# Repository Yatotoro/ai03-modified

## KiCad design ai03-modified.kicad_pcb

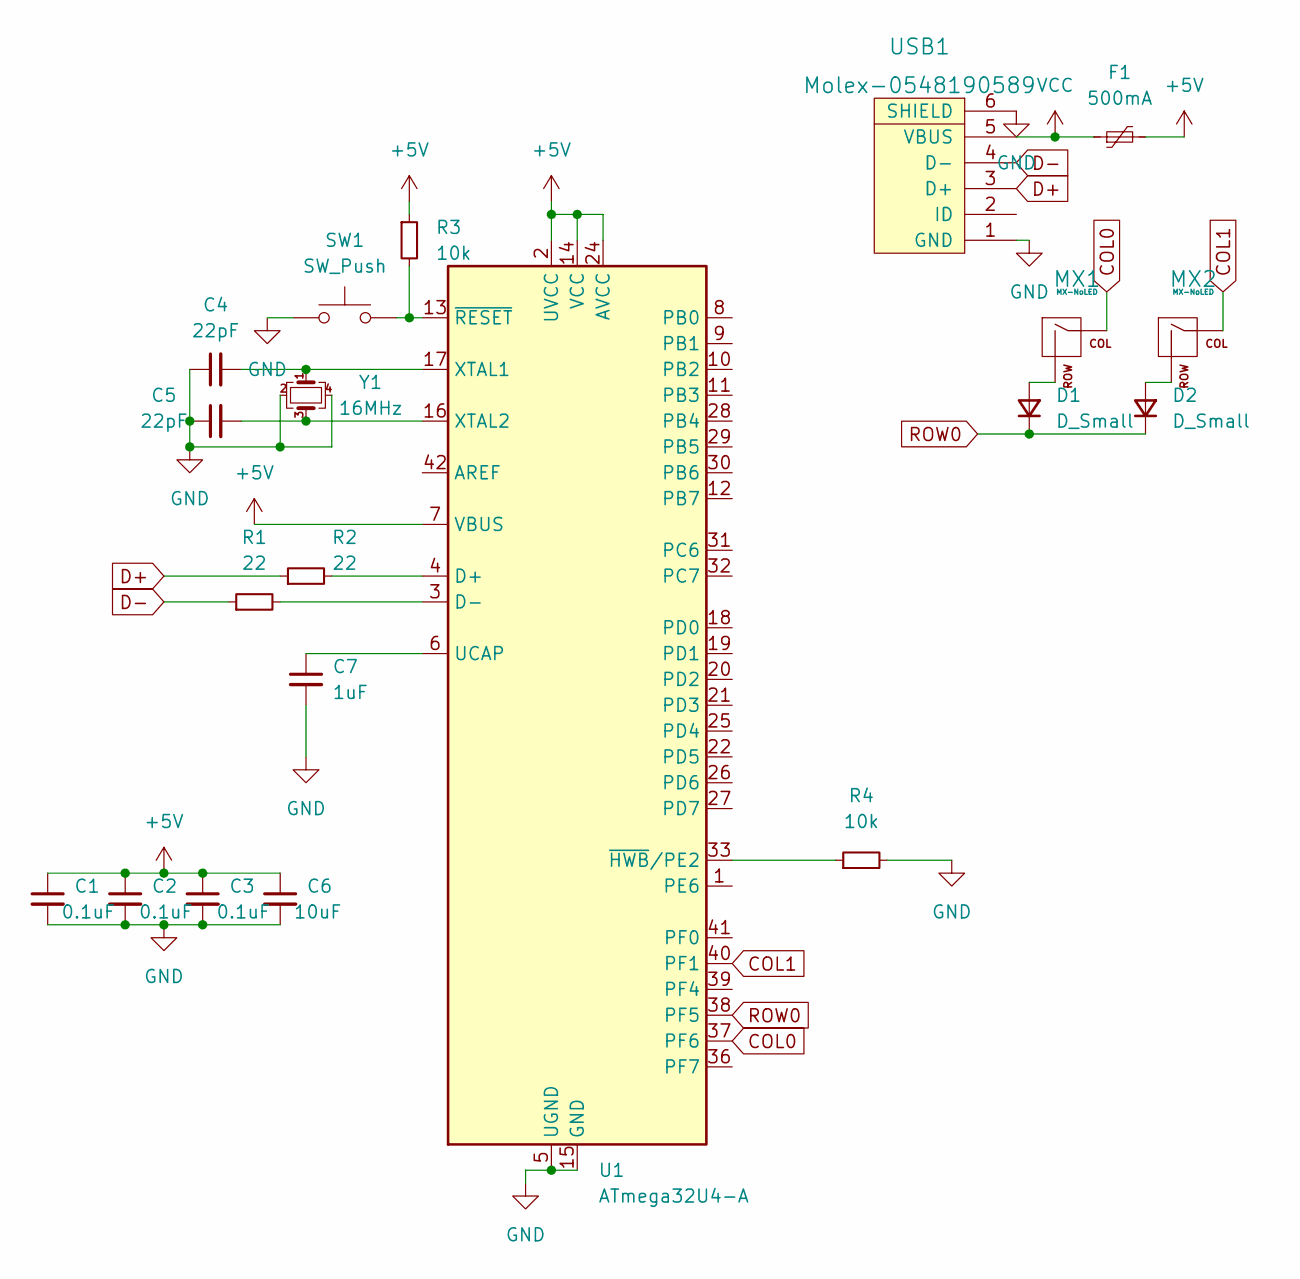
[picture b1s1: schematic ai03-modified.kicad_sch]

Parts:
C1, C2, C3: 0.1uF; C_0805_2012Metric
C4, C5: 22pF; C_0805_2012Metric
C6: 10uF; C_0805_2012Metric
C7: 1uF; C_0805_2012Metric
D1, D2: D_Small; D_SOD-123
F1: 500mA; Fuse_1206_3216Metric
MX1, MX2: MX-NoLED; MX-1U-NoLED
R1, R2: 22; R_0805_2012Metric
R3, R4: 10k; R_0805_2012Metric
SW1: SW_Push; SKQG-1155865
U1: ATmega32U4-A; LQFP-44_10x10mm_P0.8mm
USB1: Molex-0548190589; Molex-0548190519
Y1: 16MHz; Crystal_SMD_3225-4Pin_3.2x2.5mm

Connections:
+5V: C1.1, C2.1, C3.1, C6.1, F1.2, R3.1, U1.2 (UVCC), U1.7 (VBUS), U1.14 (VCC), U1.24 (AVCC), U1.34 (VCC), U1.44 (AVCC)
COL0: MX1.1 (COL), U1.37 (PF6)
COL1: MX2.1 (COL), U1.40 (PF1)
D+: R2.1, USB1.3 (D+)
D-: R1.1, USB1.4 (D-)
GND: C1.2, C2.2, C3.2, C4.1, C5.1, C6.2, C7.2, R4.2, SW1.1, U1.5 (UGND), U1.15 (GND), U1.23 (GND), U1.35 (GND), U1.43 (GND), USB1.1 (GND), USB1.6 (SHIELD), Y1.2, Y1.4
unnamed: C4.2, U1.17 (XTAL1), Y1.1
unnamed: C5.2, U1.16 (XTAL2), Y1.3
unnamed: C7.1, U1.6 (UCAP)
unnamed: D1.2 (A), MX1.2 (ROW)
unnamed: D2.2 (A), MX2.2 (ROW)
unnamed: R1.2, U1.3 (D-)
unnamed: R2.2, U1.4 (D+)
unnamed: R3.2, SW1.2, U1.13 (~RESET)
unnamed: R4.1, U1.33 (~HWB/PE2)
ROW0: D1.1 (K), D2.1 (K), U1.38 (PF5)
VCC: F1.1, USB1.5 (VBUS)

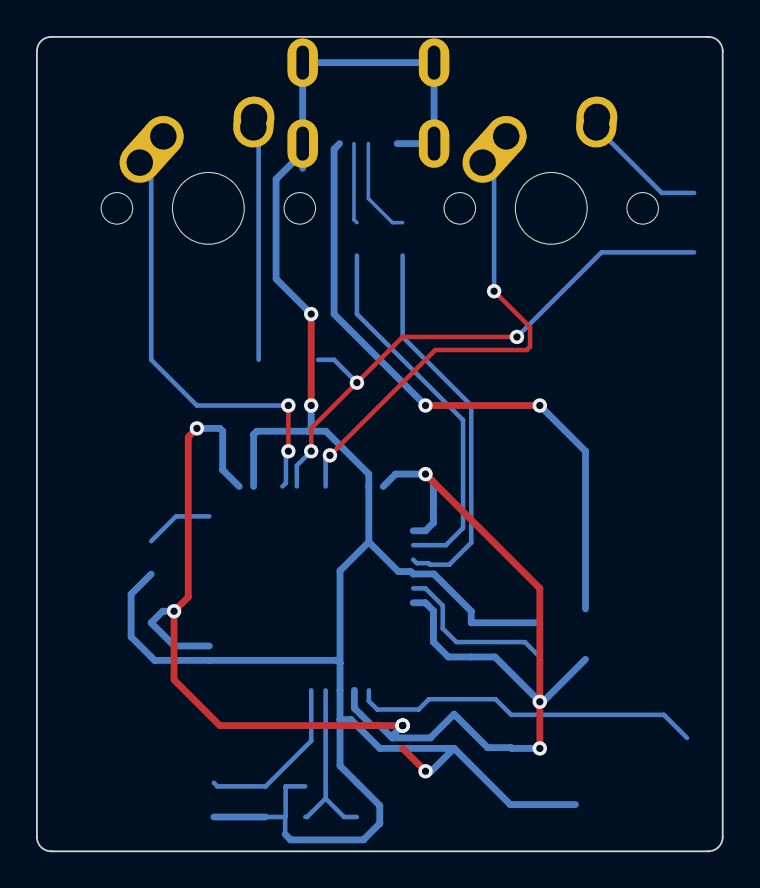
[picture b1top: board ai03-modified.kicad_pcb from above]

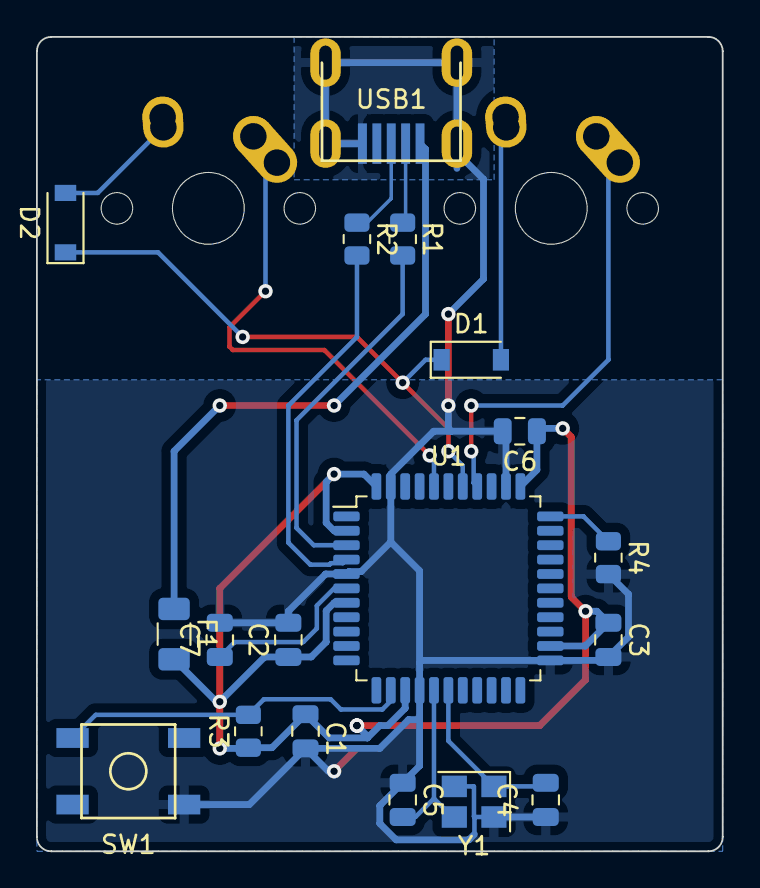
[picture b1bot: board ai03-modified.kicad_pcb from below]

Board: 2 copper layers, 38.1 x 45.2 mm, 20 parts (18 on the bottom side), 17 nets.

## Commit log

2022-10-01 Add submodules
2022-10-01 Footprint lib
2022-10-01 Add submodules 2
2022-10-01 Schematic complete
2022-10-02 Finish
2022-10-02 FillZone
